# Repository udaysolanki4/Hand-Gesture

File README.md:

# Hand-Gesture
Robots are controlled using hand gesture because robots
need a helping hand whether it may be any function, without
human robots cannot be operated. The main purpose of
using hand gestures is that it provides a more schematic
way of controlling the robot and with this feature robot can
be used as a wheelchair or as a spy robot or for vigilance. As
human hand gestures are natural, with the help of wireless
communication, it is easier to interact with the robot in a
more-friendly way. The robot’s movement depends on the
gestures made by hand. The objective of this paper is to
build a wireless, hand gesture controlled robot using an
Arduino Uno, an accelerometer, and a RF transmitter and a
RF receiver set. The Arduino Uno microcontroller reads the
analog output values i.e., x-axis and y-axis values of the
accelerometer and converts that analog value to respective
digital value. The values are given a specific function by the
use of the Arduino software. The digital values are processed
by the Arduino Uno microcontroller and according to the tilt
of the accelerometer sensor mounted on the hand, it sends
the commands to the RF transmitter which sends the signal
to the receiver and there these signals are processed by the
receiver end which drives the motor to a particular direction
in which we have set it to move. The robot moves forward,
backward, right and left when we tilt our palm to forward,
backward, right and left respectively and the robot stops
when our palm is parallel to the ground.

## Components

### Arduino nano
Arduino nano It is a microcontroller board based on
ATmega328 which has 14 digital I/O and 6 analog pins. It
has everything that is needed to support the microcontroller.
Simply connect it to the computer with a USB cable to get
started with the Arduino Uno board. It is flexible, easy to use
hardware and software. Arduino nano can sense the
environment by receiving input from a variety of sensors
and can affect its surroundings by controlling lights, motors,
and other actuators.

### Accelerometer (ADXL335)
The ADXL335 is a small, thin, low power, complete 3-axis
accelerometer with signal conditioned voltage outputs. It has
5 pins. 3 pins is for X, Y, Z axis. First pin for power supply
(VCC), second pin for ground (GND). It operates on 3.3V from the Arduino Uno board. X
and Y axis pins are connected to A0 and A1 pin of Arduino
Uno board respectively. It can measure the static acceleration
of gravity from tilt sensing applications as well as dynamic
acceleration resulting from motion, shock or vibration and
gives corresponding analog values through X, Y, Z axis pins.

### RF Transmitter & Receiver
The transmitter module is working on the frequency of
433MHz. In the circuit, Vcc pin is connected to the + terminal.
The data pin is connected to the HT12E (Encoder) that is
transmitted or we can say that encoded data. The next pin
is GND that is connected to the ground terminal. Now the last
pin ANT this is connected to a small wire as an antenna.
The RF receiver module will receive the data which is
transferred by the gesture device. It is also working as similar
to the transmitter module- Connect the +Vcc pin to the 5volt
terminal. Connect the ground pin to the ground terminal .The
data pin is then connected to the HT12D (Decoder) .So that
we can get the decoded 4 bit data.

### Motor Driver
Motor Driver works on the concept of H-bridge. H-bridge is a
circuit which allows the voltage to flow in either direction. As
voltage need to change its direction for being able to rotate
the motor in clockwise or anti-clockwise direction. Therefore
H-bridge IC is ideal for driving a DC motor. In a single L293D
chip there are two h-Bridge circuit inside the IC which can
rotate two dc motor independently. Due to its size it is very
much used in robotic application for controlling DC motors.

### DC Motor
DC motor is used for the conversion of direct current into
mechanical motion. The mechanical motion could be rotary
or linear. The operation of DC motor is based on the principle
that when a current carrying conductor is placed in a
magnetic field, the conductor experiences a mechanical force.
The speed of a DC motor can be controlled by changing the
voltage applied to the armature or by changing the field
current. DC motors can be used for the movement of the
robotic car.

### Battery
A battery is a device consisting of one or more
electrochemical cells. A battery is device that directly
converts chemical energy to the electrical energy. The
purpose of battery is to supply 12 volts to operateDC motors.

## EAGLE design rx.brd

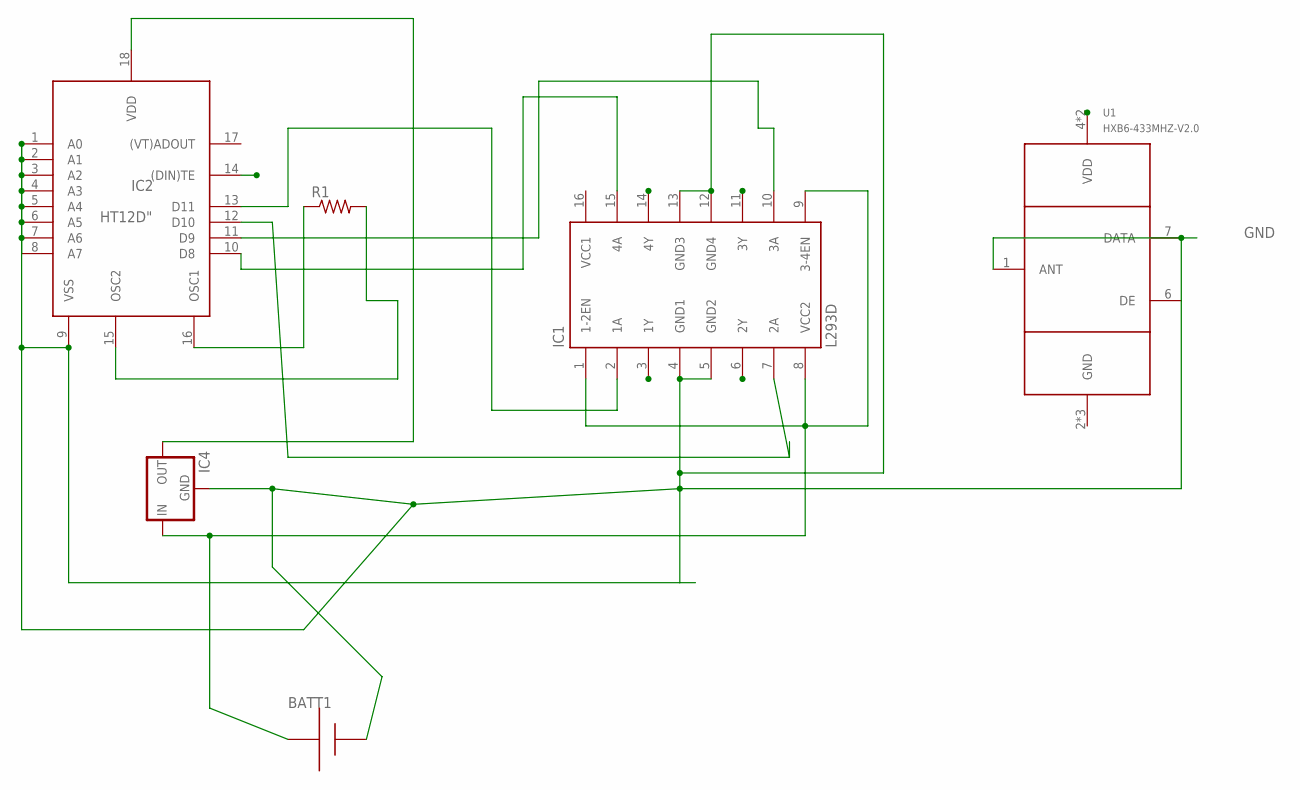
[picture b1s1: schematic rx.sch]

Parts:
BATT1: AAA; 12BH412
IC1: L293D; DIL16
IC2: HT12D"; 18-DIP-A
IC4: 78XXS
R1: R-US_0207/9; 0207/9
U1: HXB6-433MHZ-V2.0; RXB6-XXX-V

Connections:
GND: BATT1.+, IC1.4 (GND1), IC1.5 (GND2), IC1.12 (GND4), IC1.13 (GND3), IC2.1 (A0), IC2.2 (A1), IC2.3 (A2), IC2.4 (A3), IC2.5 (A4), IC2.6 (A5), IC2.7 (A6), IC2.8 (A7), IC2.9 (VSS), IC4.GND, U1.1 (ANT), U1.6 (DE), U1.7 (DATA)
unnamed: IC2.18 (VDD), IC4.OUT
unnamed: IC2.16 (OSC1), R1.1
unnamed: IC2.15 (OSC2), R1.2
unnamed: IC1.2 (1A), IC2.13 (D11)
unnamed: IC1.7 (2A), IC2.12 (D10)
unnamed: IC1.10 (3A), IC2.11 (D9)
unnamed: IC1.15 (4A), IC2.10 (D8)
unnamed: BATT1.-, IC1.1 (1-2EN), IC1.8 (VCC2), IC1.9 (3-4EN), IC4.IN
VCC1: IC1.16 (VCC1)
VDD: U1.4 (VDD), U1.5 (VDD)

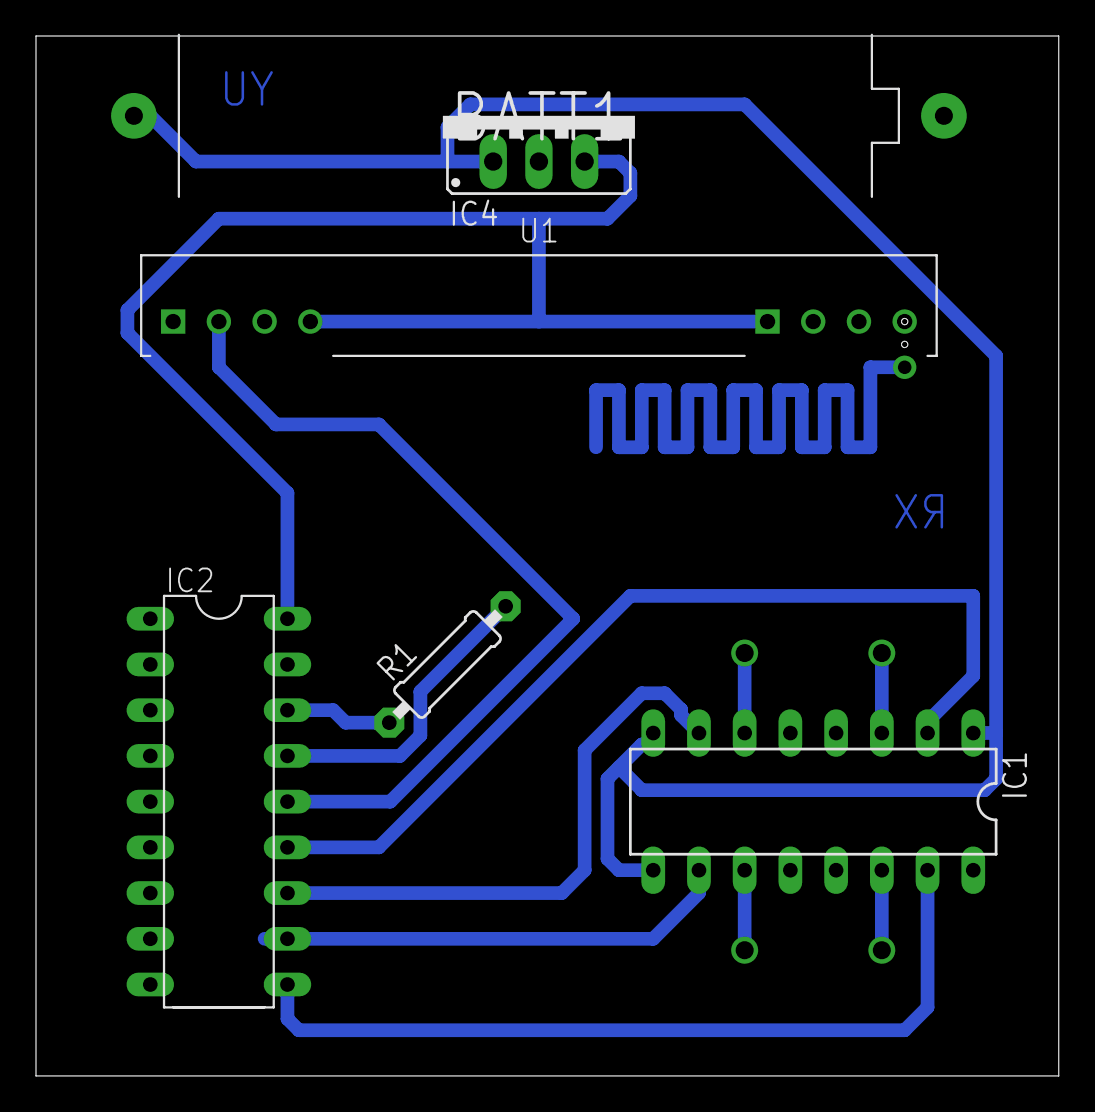
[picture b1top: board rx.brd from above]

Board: 2 copper layers, 56.8 x 57.8 mm, 6 parts (0 on the bottom side), 10 nets.

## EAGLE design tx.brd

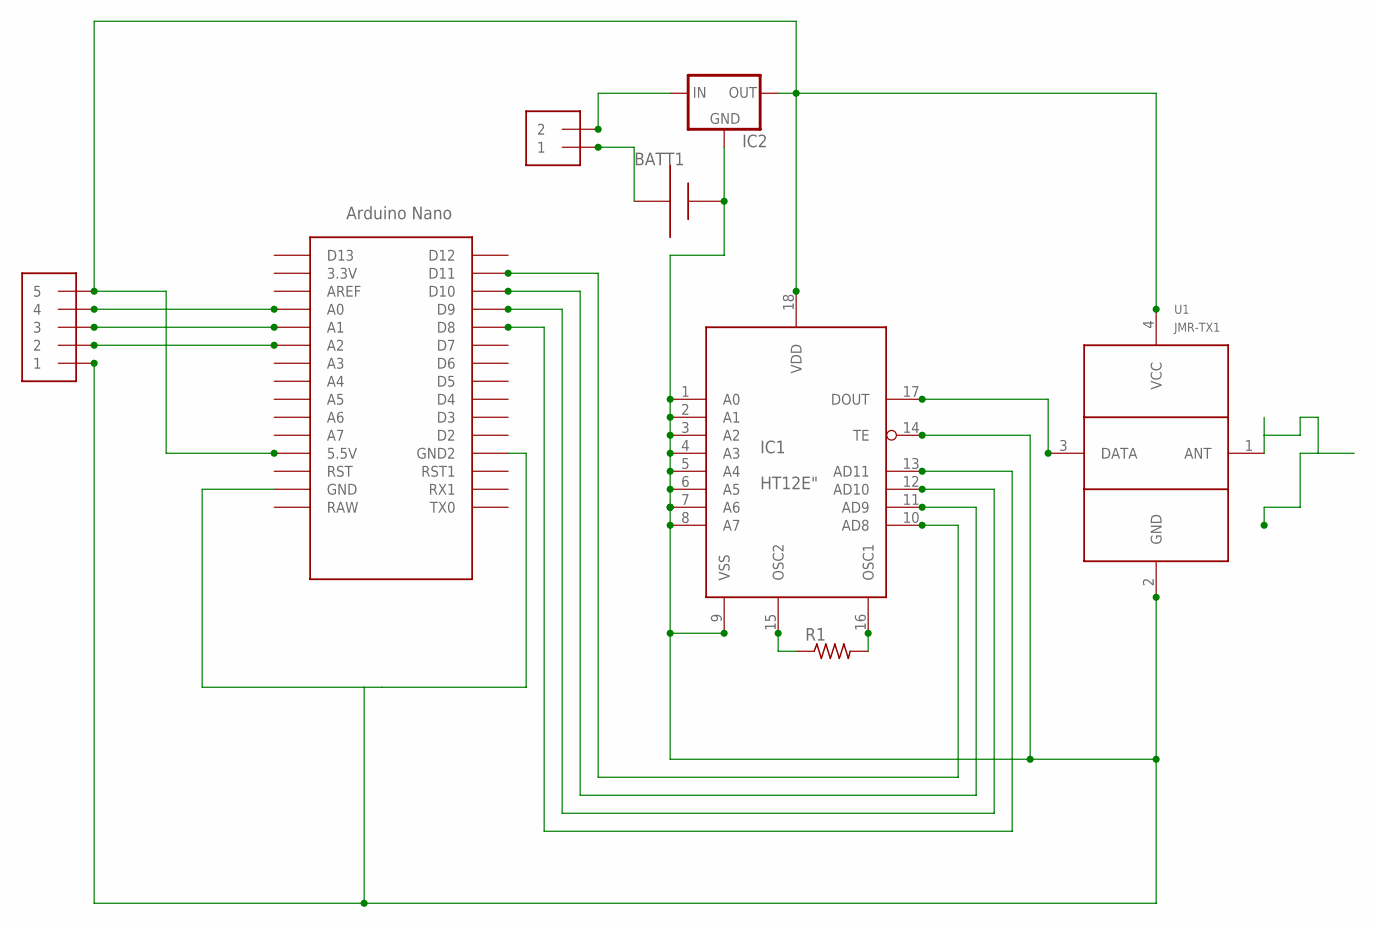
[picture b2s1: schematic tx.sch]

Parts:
BATT1: AAA; 12BH412
IC1: HT12E"; 18-DIP-A
IC2: 78MXXL
J1: 1X5; 1X05-3.5MM
J2: 1X2-3.5MM
R1: R-US_0207/9; 0207/9
U1: JMR-TX1
U$2: NANO

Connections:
GND: BATT1.+, IC1.1 (A0), IC1.2 (A1), IC1.3 (A2), IC1.4 (A3), IC1.5 (A4), IC1.6 (A5), IC1.7 (A6), IC1.8 (A7), IC1.9 (VSS), IC1.14 (TE), IC2.GND, J1.1, U1.2 (GND), U$2.GND, U$2.GND1 (GND2)
unnamed: IC1.15 (OSC2), R1.1
unnamed: IC2.IN, J2.2
unnamed: BATT1.-, J2.1
unnamed: IC1.16 (OSC1), R1.2
unnamed: IC1.13 (AD11), U$2.D8
unnamed: IC1.17 (DOUT), U1.3 (DATA)
unnamed: IC1.12 (AD10), U$2.D9
unnamed: IC1.11 (AD9), U$2.D10
unnamed: IC1.10 (AD8), U$2.D11
unnamed: J1.4, U$2.A0
unnamed: J1.3, U$2.A1
unnamed: J1.2, U$2.A2
VCC: IC1.18 (VDD), IC2.OUT, J1.5, U1.4 (VCC), U$2.5V (5.5V)

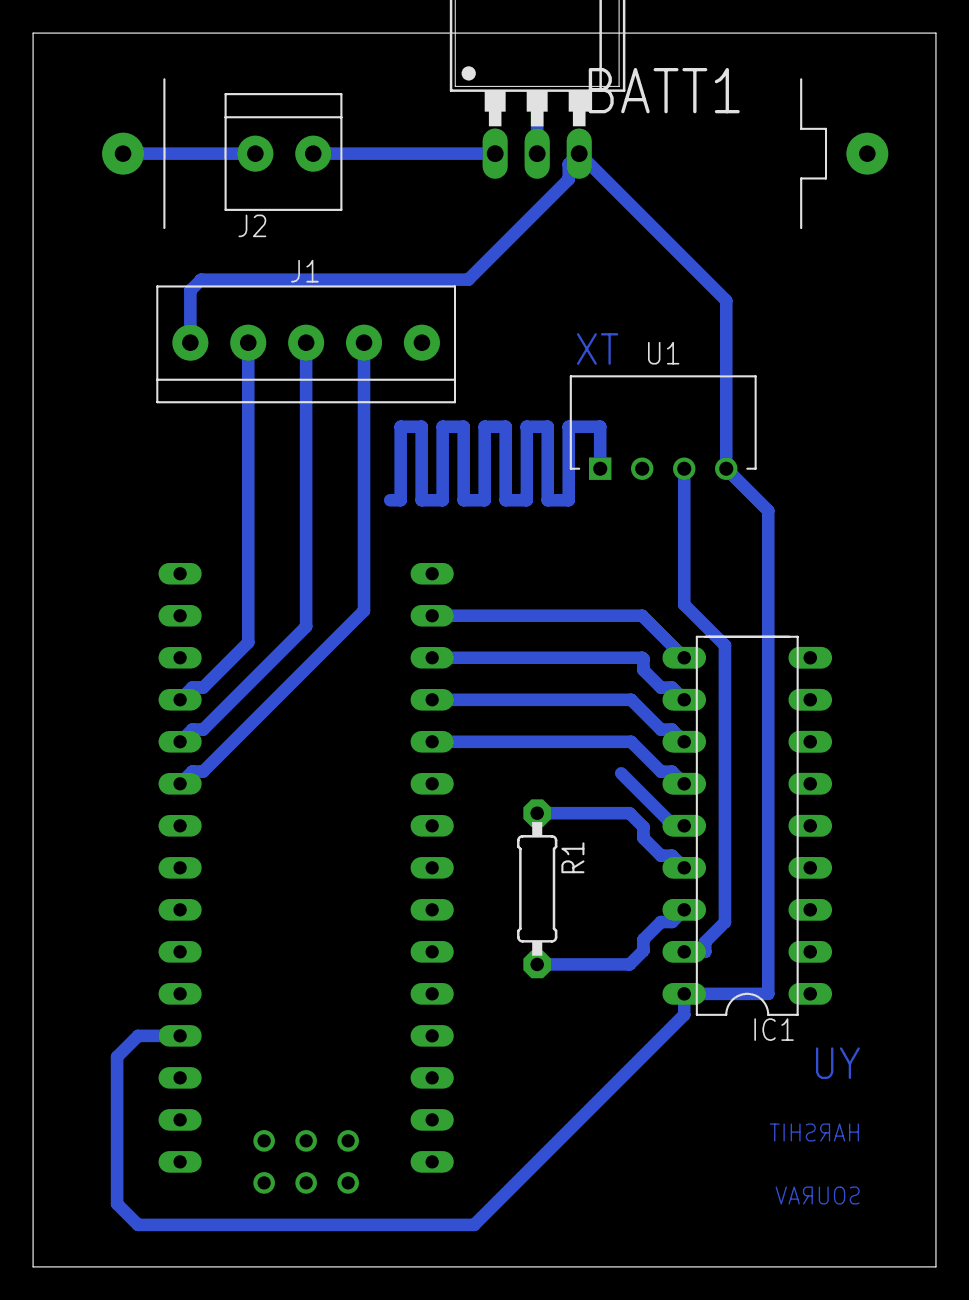
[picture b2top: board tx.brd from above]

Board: 2 copper layers, 54.6 x 74.6 mm, 8 parts (0 on the bottom side), 14 nets.

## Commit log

2019-05-06 arduino code
    the code contains 2 axis access. I'm using ADXL335 Accelerometer Sensor need to calibrate when you are testing it for movable if conditions.
2019-05-06 etching files
    these 2 files are the receiver board file which contains motor driver L293D and HT12D ic which used to decode the data received by Rx of rf module and a voltage regulator 7805 ic. Transmitter file co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
2019-05-06 schematic files
    I'm attaching the schematic AutoCAD Eagle file where I have designed PCB.
2019-05-06 board file
    I'm attaching the board AutoCAD Eagle file where I have designed PCB.
